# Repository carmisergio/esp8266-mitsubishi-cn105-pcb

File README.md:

# ESP8266 Mitsubishi CN105 interface PCB
A simple PCB that allows control of Mitsubishi AC units via CN105.

Designed to be used with [MitsubishiCN105ESPHome](github.com/echavet/MitsubishiCN105ESPHome).

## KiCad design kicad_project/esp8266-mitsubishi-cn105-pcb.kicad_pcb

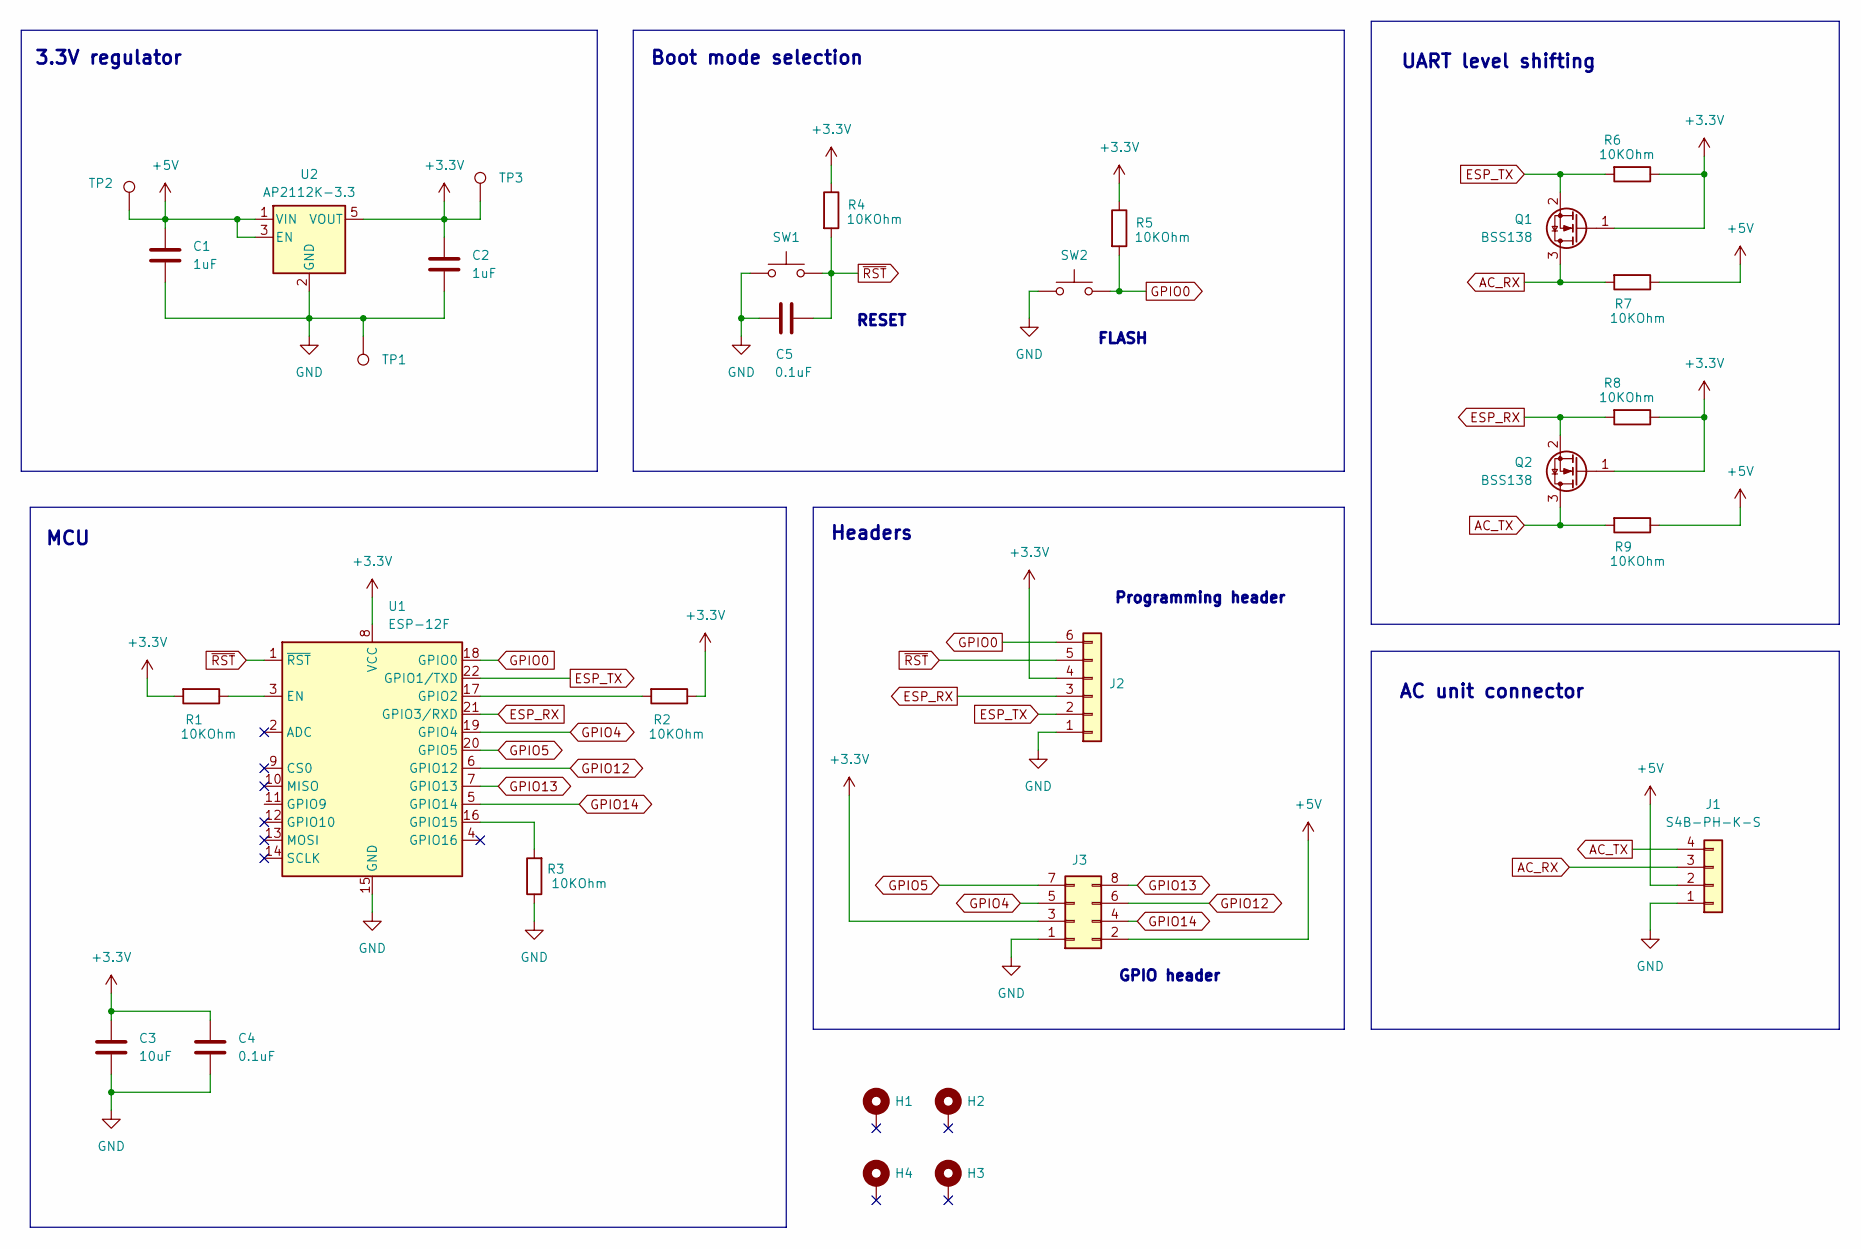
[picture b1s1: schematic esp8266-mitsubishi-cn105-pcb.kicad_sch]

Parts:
C1, C2: 1uF; C_0805_2012Metric_Pad1.18x1.45mm_HandSolder
C3: 10uF; C_1206_3216Metric_Pad1.33x1.80mm_HandSolder
C4, C5: 0.1uF; C_0603_1608Metric_Pad1.08x0.95mm_HandSolder
H1, H2, H3, H4: MountingHole_Pad; MountingHole_3.2mm_M3_DIN965_Pad
J1: S4B-PH-K-S; JST_PH_S4B-PH-K_1x04_P2.00mm_Horizontal
J2: Conn_01x06; PinHeader_1x06_P2.54mm_Vertical
J3: Conn_02x04_Odd_Even; PinHeader_2x04_P1.27mm_Vertical
Q1, Q2: BSS138; SOT-23
R1, R2, R3, R4, R5, R6, R7, R8, R9: 10KOhm; C_0603_1608Metric_Pad1.08x0.95mm_HandSolder
SW1, SW2: SW_Push; SW_Tactile_SPST_NO_Straight_CK_PTS636Sx25SMTRLFS
TP1, TP2, TP3: TestPoint; TestPoint_Pad_D2.0mm
U1: ESP-12F; ESP-12E
U2: AP2112K-3.3; SOT-23-5

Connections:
+3.3V: C2.1, C3.1, C4.1, J2.4, J3.3, Q1.1 (G), Q2.1 (G), R1.2, R2.1, R4.1, R5.1, R6.1, R8.1, TP3.1, U1.8 (VCC), U2.5 (VOUT)
+5V: C1.1, J1.2, J3.2, R7.1, R9.1, TP2.1, U2.1 (VIN), U2.3 (EN)
AC_RX: J1.3, Q1.3 (D), R7.2
AC_TX: J1.4, Q2.3 (D), R9.2
ESP_RX: J2.3, Q2.2 (S), R8.2, U1.21 (GPIO3/RXD)
ESP_TX: J2.2, Q1.2 (S), R6.2, U1.22 (GPIO1/TXD)
GND: C1.2, C2.2, C3.2, C4.2, C5.1, J1.1, J2.1, J3.1, R3.1, SW1.1, SW2.1, TP1.1, U1.15 (GND), U2.2 (GND)
GPIO0: J2.6, R5.2, SW2.2, U1.18 (GPIO0)
GPIO4: J3.5, U1.19 (GPIO4)
GPIO5: J3.7, U1.20 (GPIO5)
GPIO12: J3.6, U1.6 (GPIO12)
GPIO13: J3.8, U1.7 (GPIO13)
GPIO14: J3.4, U1.5 (GPIO14)
unnamed: R1.1, U1.3 (EN)
unnamed: R2.2, U1.17 (GPIO2)
unnamed: R3.2, U1.16 (GPIO15)
~RST: C5.2, J2.5, R4.2, SW1.2, U1.1 (~RST)

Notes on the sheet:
Boot mode selection
GPIO header
RESET
3.3V regulator
Headers
FLASH
Programming header
MCU
AC unit connector
UART level shifting

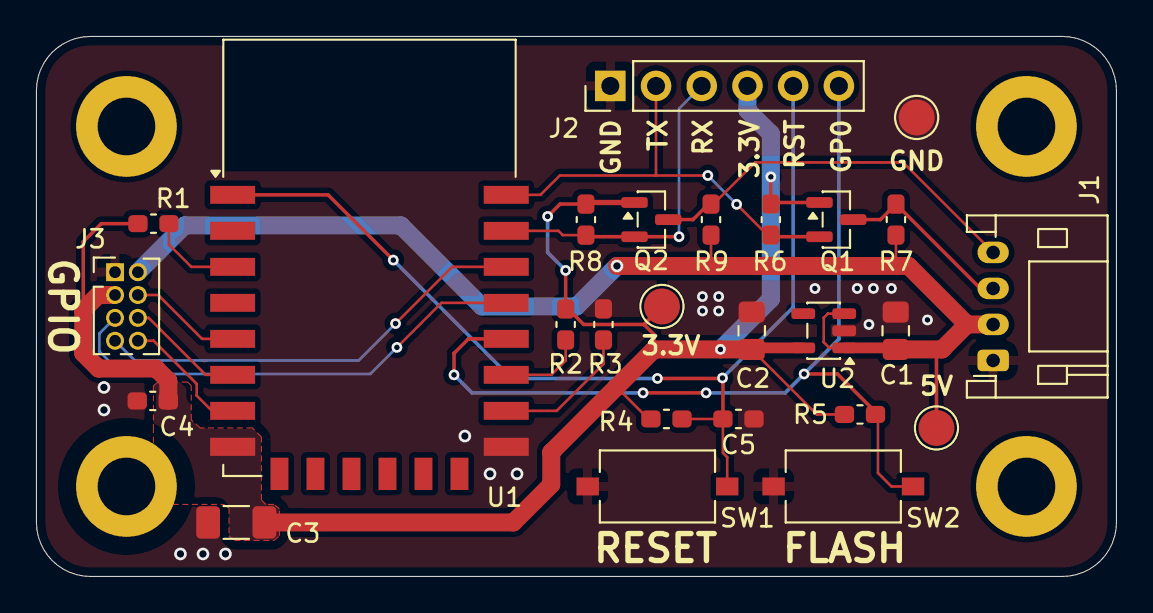
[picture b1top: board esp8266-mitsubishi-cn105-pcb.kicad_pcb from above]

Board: 2 copper layers, 60.0 x 30.0 mm, 30 parts (0 on the bottom side), 17 nets.

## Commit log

2026-02-12 Initial project structure
2026-02-13 Final (hopefully) production design
2026-02-15 Final production design

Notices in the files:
kicad_project/esp8266-mitsubishi-cn105-pcb.kicad_pcb:
(c) 2026 - Sergio Carmine
